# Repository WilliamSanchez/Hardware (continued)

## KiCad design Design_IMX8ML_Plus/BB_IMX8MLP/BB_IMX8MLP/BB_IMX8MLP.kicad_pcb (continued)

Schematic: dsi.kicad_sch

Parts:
C198, C199: 100nF; C_0402_1005Metric
J15: DSI; Hirose_FH12-24S-0.5SH_1x24-1MP_P0.50mm_Horizontal
R96, R97, R98, R99: 10K; R_0402_1005Metric
U21, U28, U29: D3V3F4U10LP-7; DFN10_U-DFN2510-10_DIO
U52: FXMA2102L8X; MICROPAK8_1P6X1P6_ONS

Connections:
/CSI_DSI/DSI/1v8: C198.1, R98.1, R99.1, U52.1 (VCCA)
/CSI_DSI/DSI/3v3: C199.1, R96.1, R97.1, U52.8 (VCCB)
/CSI_DSI/DSI/I2C2_DTA_LVDS0: R97.2, U52.6 (B1)
/CSI_DSI/DSI/I2C2_SCL: R98.2, U52.2 (A0)
/CSI_DSI/DSI/I2C2_SCL_LVDS0: R96.2, U52.7 (B0)
/CSI_DSI/DSI/I2C2_SDA: R99.2, U52.3 (A1)
DSI1_CLK_N: J15.3, U28.1 (I/O), U28.10 (I/O); also elsewhere on the board
DSI1_CLK_P: J15.2, U28.2 (I/O), U28.9 (I/O); also elsewhere on the board
DSI1_D0_N: J15.15, U29.5 (I/O), U29.6 (I/O); also elsewhere on the board
DSI1_D0_P: J15.14, U29.4 (I/O), U29.7 (I/O); also elsewhere on the board
DSI1_D1_N: J15.12, U29.2 (I/O), U29.9 (I/O); also elsewhere on the board
DSI1_D1_P: J15.11, U29.1 (I/O), U29.10 (I/O); also elsewhere on the board
DSI1_D2_N: J15.9, U21.5 (I/O), U21.6 (I/O); also elsewhere on the board
DSI1_D2_P: J15.8, U21.4 (I/O), U21.7 (I/O); also elsewhere on the board
DSI1_D3_N: J15.6, U21.2 (I/O), U21.9 (I/O); also elsewhere on the board
DSI1_D3_P: J15.5, U21.1 (I/O), U21.10 (I/O); also elsewhere on the board
GND: C198.2, C199.2, J15.1, J15.4, J15.7, J15.10, J15.13, J15.16, U52.4 (GND); also elsewhere on the board

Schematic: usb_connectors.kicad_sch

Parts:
C47, C51, C54, C55, C60, C61, C150, C151, C152, C153, C209: 100nF; C_0402_1005Metric
C48, C49, C56, C57, C194, C195, C208: 100uF; C_1210_3225Metric
C50, C58, C64: 1nF; C_0402_1005Metric
C52, C53, C59: 10uF; C_0603_1608Metric
FB1, FB2, FB3: 220R@100MHz; L_0603_1608Metric
J9: GSB311231HR; AMPHENOL_GSB311231HR; PARTREV D1
J14: USB_C_Receptacle; USB_C_Receptacle_Molex_105450-0101
R16: 887K; R_0402_1005Metric
R39, R40, R41, R61, R85: 100K; R_0402_1005Metric
R59, R60, R86: 0; R_0402_1005Metric
R84: 15K; R_0402_1005Metric
U9, U10, U40: PCMF3USB3S; Nexperia_WLCSP-15_6-3-6_2.37x1.17mm_Layout6x3_P0.4mm
U11, U12, U13: AOZ1353DI-01; DFN-12-1EP_3x3mm_P0.5mm_EP1.6x2.5mm
U56: TUSB321; Texas_X2QFN-12_1.6x1.6mm_P0.4mm

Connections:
5V_BB: C52.1, C53.1, C59.1, C208.1, C209.1, U11.10 (Vin), U11.11 (Vin), U11.12 (Vin), U12.10 (Vin), U12.11 (Vin), U12.12 (Vin), U13.10 (Vin), U13.11 (Vin), U13.12 (Vin), U56.12 (VDD); also elsewhere on the board
/USB/usb_connectors/1v8: R39.1, R40.1, R61.1
/USB/usb_connectors/USBH1D+: J14.A6 (D+), J14.B6 (D+), U40.C5 (CH3_OUT+)
/USB/usb_connectors/USBH1D-: J14.A7 (D-), J14.B7 (D-), U40.C6 (CH3_OUT-)
/USB/usb_connectors/USBH1SSRX+: J14.B11 (RX1+), U40.C3 (CH2_OUT+)
/USB/usb_connectors/USBH1SSRX-: J14.B10 (RX1-), U40.C4 (CH2_OUT-)
/USB/usb_connectors/USBH1SSTX+: J14.A2 (TX1+), U40.C1 (CH1_OUT+)
/USB/usb_connectors/USBH1SSTX-: J14.A3 (TX1-), U40.C2 (CH1_OUT-)
/USB/usb_connectors/USBH2D+: J9.12 (D+_2), U10.C1 (CH1_OUT+)
/USB/usb_connectors/USBH2D-: J9.11 (D-_2), U10.C2 (CH1_OUT-)
/USB/usb_connectors/USBH2SSRX+: J9.15 (SSRX+_2), U10.C5 (CH3_OUT+)
/USB/usb_connectors/USBH2SSRX-: J9.14 (SSRX-_2), U10.C6 (CH3_OUT-)
/USB/usb_connectors/USBH2SSTX+: J9.18 (SSTX+_2), U10.C3 (CH2_OUT+)
/USB/usb_connectors/USBH2SSTX-: J9.17 (SSTX-_2), U10.C4 (CH2_OUT-)
/USB/usb_connectors/USBH3D+: J9.3 (D+_1), U9.C1 (CH1_OUT+)
/USB/usb_connectors/USBH3D-: J9.2 (D-_1), U9.C2 (CH1_OUT-)
/USB/usb_connectors/USBH3SSRX+: J9.6 (SSRX+_1), U9.C5 (CH3_OUT+)
/USB/usb_connectors/USBH3SSRX-: J9.5 (SSRX-_1), U9.C6 (CH3_OUT-)
/USB/usb_connectors/USBH3SSTX+: J9.9 (SSTX+_1), U9.C3 (CH2_OUT+)
/USB/usb_connectors/USBH3SSTX-: J9.8 (SSTX-_1), U9.C4 (CH2_OUT-)
/USB/usb_connectors/USB_1_EN: R41.1, U13.9 (ENB)
/USB/usb_connectors/USB_1_ID: R40.2, U56.9 (ID)
/USB/usb_connectors/USB_1_OC#: R61.2, U13.4 (FLTB)
/USB/usb_connectors/USB_1_VBUS: R85.1, R86.1
/USB/usb_connectors/VBUS: C48.1, C49.1, C64.1, FB1.2, J14.A4 (VBUS), J14.A9 (VBUS), J14.B4 (VBUS), J14.B9 (VBUS), R16.1, R86.2
/USB/usb_connectors/VBUSH_1: C50.1, C194.1, C195.1, FB2.2, J9.1 (VBUS_1)
/USB/usb_connectors/VBUSH_2: C56.1, C57.1, C58.1, FB3.2, J9.10 (VBUS_2)
GND: C47.2, C48.2, C49.2, C50.2, C51.2, C52.2, C53.2, C54.2, C55.2, C56.2, C57.2, C58.2, C59.2, C60.2, C61.2, C64.2, C194.2, C195.2, C208.2, C209.2, J9.4 (GND_1), J9.7 (GND_DRAIN_1), J9.13 (GND_2), J9.16 (GND_DRAIN_2), R41.2, R84.2, R85.2, U9.B1 (GND_CH1), U9.B2 (GND_CH2), U9.B3 (GND_CH3), U10.B1 (GND_CH1), U10.B2 (GND_CH2), U10.B3 (GND_CH3), U11.7 (GND), U11.13 (EXP), U12.7 (GND), U12.13 (EXP), U13.7 (GND), U13.13 (EXP), U40.B1 (GND_CH1), U40.B2 (GND_CH2), U40.B3 (GND_CH3), U56.10 (GND); also elsewhere on the board
unnamed: C47.1, FB2.1, U11.1 (Vout), U11.2 (Vout), U11.3 (Vout)
unnamed: C55.1, FB3.1, U12.1 (Vout), U12.2 (Vout), U12.3 (Vout)
unnamed: C61.1, FB1.1, U13.1 (Vout), U13.2 (Vout), U13.3 (Vout)
unnamed: J9.SH1 (SHIELD), J9.SH2 (SHIELD), J9.SH3 (SHIELD), J9.SH4 (SHIELD)
unnamed: J14.A5 (CC1), U56.1 (CC1)
unnamed: J14.B5 (CC2), U56.2 (CC2)
unnamed: J14.A1 (GND), J14.A12 (GND), J14.B1 (GND), J14.B12 (GND)
unnamed: C151.1, U9.A3 (CH2_IN+)
unnamed: C150.1, U9.A4 (CH2_IN-)
unnamed: C153.1, U10.A3 (CH2_IN+)
unnamed: C152.1, U10.A4 (CH2_IN-)
unnamed: R60.1, U11.4 (FLTB)
unnamed: C51.1, U11.5 (SS)
unnamed: R59.1, U12.4 (FLTB)
unnamed: C54.1, U12.5 (SS)
unnamed: R84.1, U13.8 (ILIM)
unnamed: C60.1, U13.5 (SS)
unnamed: R16.2, U56.5 (VBUS_DET)
unnamed: R39.2, U56.6 (~VCONN_FAULT)
USB1_D_N: U40.A6 (CH3_IN-); also elsewhere on the board
USB1_D_P: U40.A5 (CH3_IN+); also elsewhere on the board
USB1_RX_N: U40.A4 (CH2_IN-); also elsewhere on the board
USB1_RX_P: U40.A3 (CH2_IN+); also elsewhere on the board
USB1_TX_N: U40.A2 (CH1_IN-); also elsewhere on the board
USB1_TX_P: U40.A1 (CH1_IN+); also elsewhere on the board
USBH2_D+: U10.A1 (CH1_IN+); also elsewhere on the board
USBH2_D-: U10.A2 (CH1_IN-); also elsewhere on the board
USBH2_PRT_CTL: R59.2, U12.8 (ILIM); also elsewhere on the board
USBH2_SSRX+: U10.A5 (CH3_IN+); also elsewhere on the board
USBH2_SSRX-: U10.A6 (CH3_IN-); also elsewhere on the board
USBH2_SSTX+: C153.2; also elsewhere on the board
USBH2_SSTX-: C152.2; also elsewhere on the board
USBH3_D+: U9.A1 (CH1_IN+); also elsewhere on the board
USBH3_D-: U9.A2 (CH1_IN-); also elsewhere on the board
USBH3_PRT_CTL: R60.2, U11.8 (ILIM); also elsewhere on the board
USBH3_SSRX+: U9.A5 (CH3_IN+); also elsewhere on the board
USBH3_SSRX-: U9.A6 (CH3_IN-); also elsewhere on the board
USBH3_SSTX+: C151.2; also elsewhere on the board
USBH3_SSTX-: C150.2; also elsewhere on the board

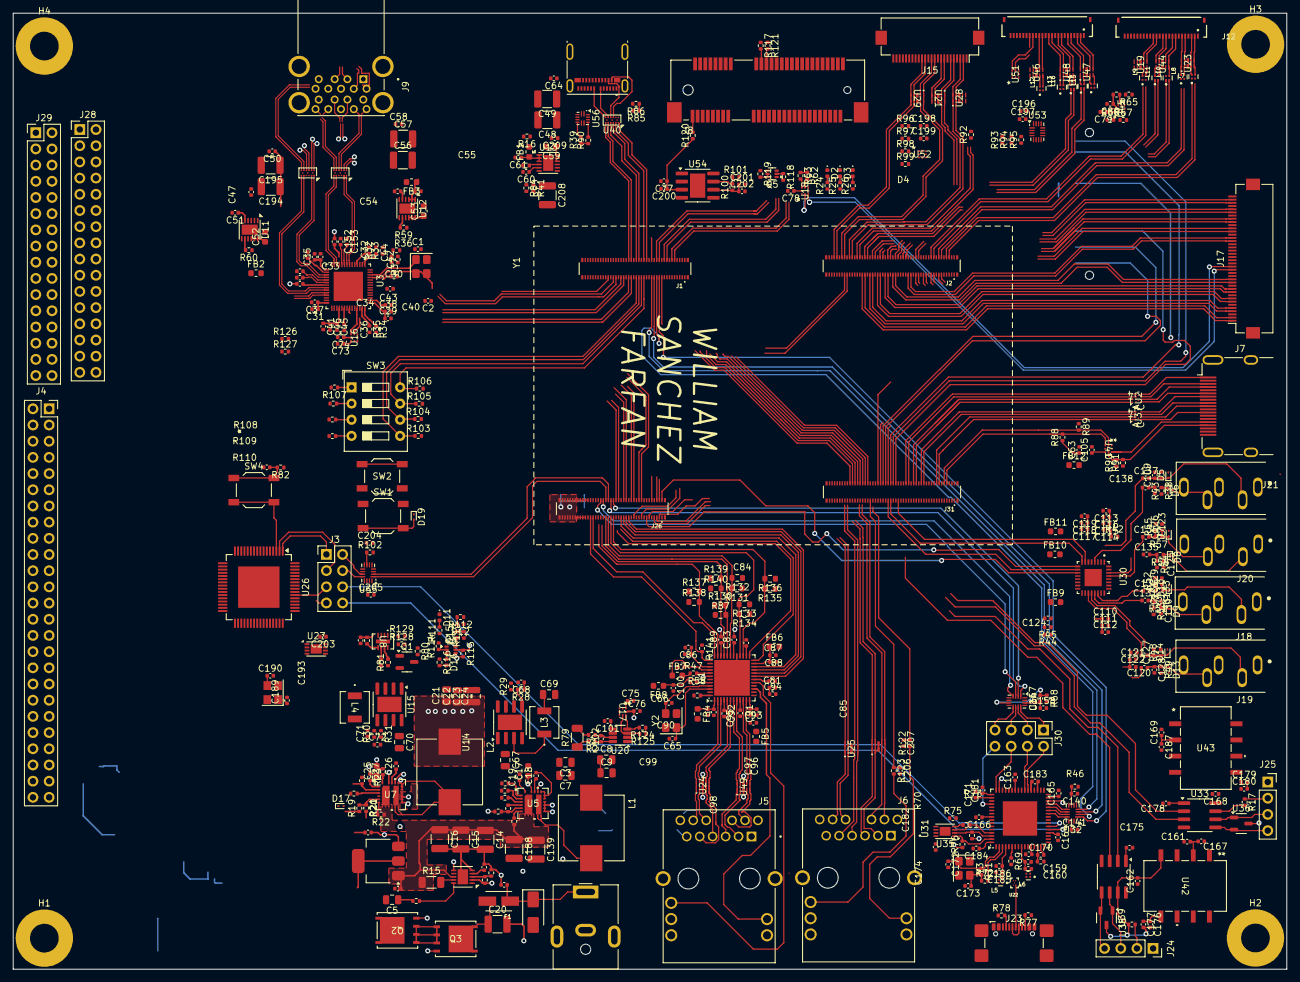
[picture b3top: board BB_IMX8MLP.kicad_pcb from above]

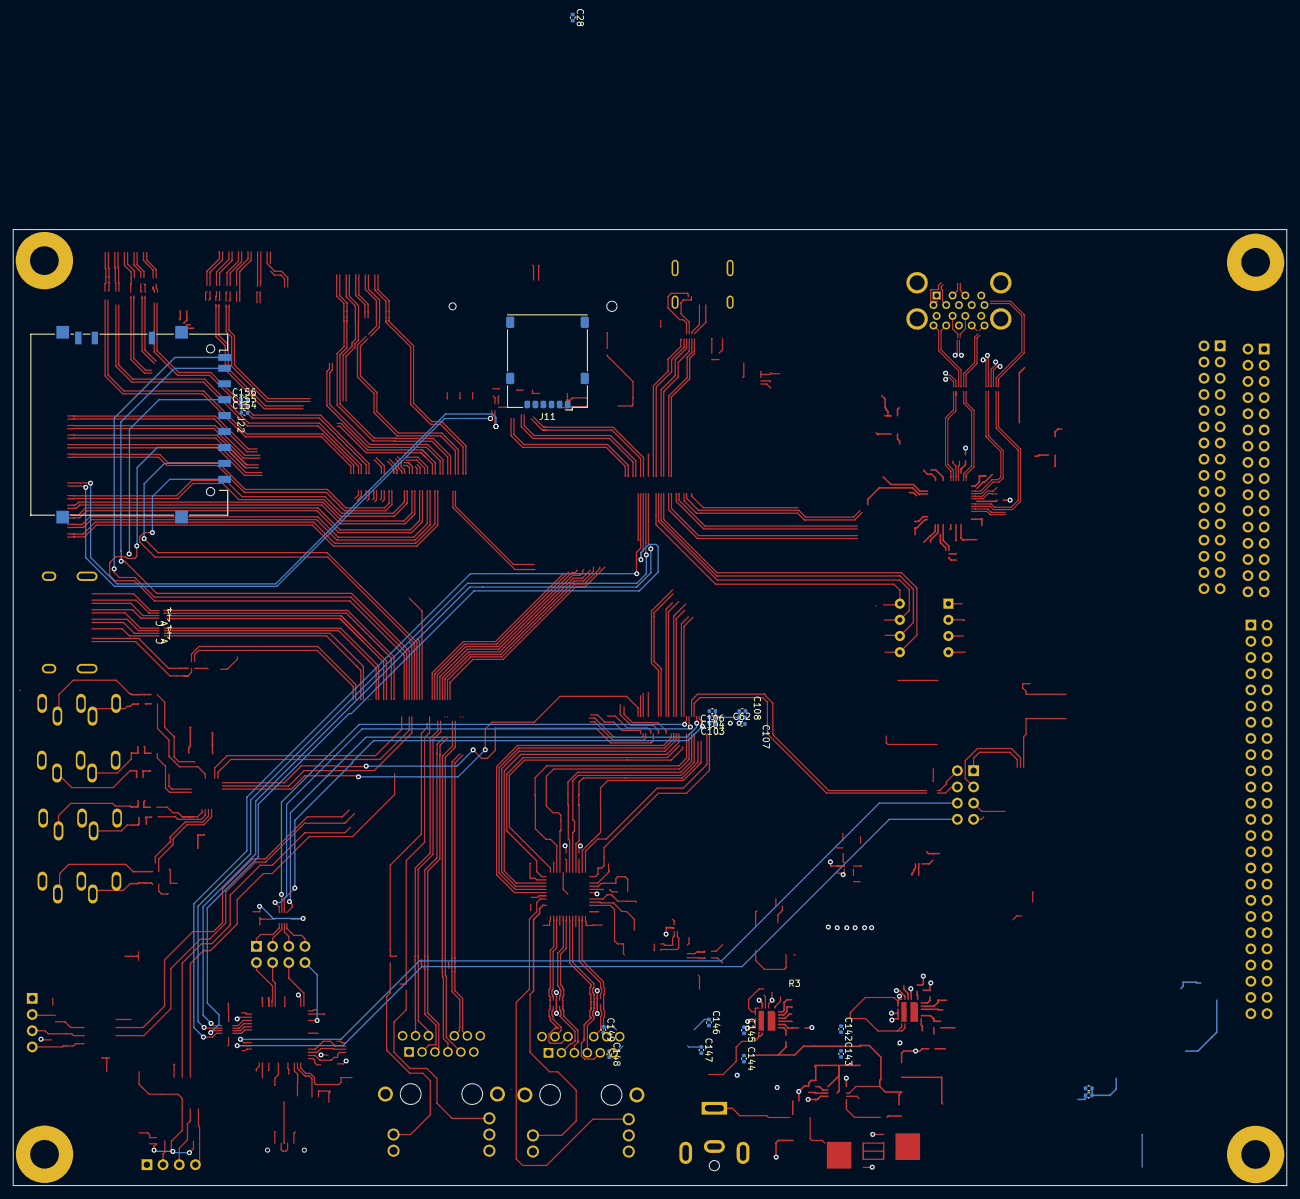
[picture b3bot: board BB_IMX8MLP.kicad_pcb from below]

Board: 4 copper layers, 199.8 x 150.0 mm, 496 parts (22 on the bottom side), 499 nets.

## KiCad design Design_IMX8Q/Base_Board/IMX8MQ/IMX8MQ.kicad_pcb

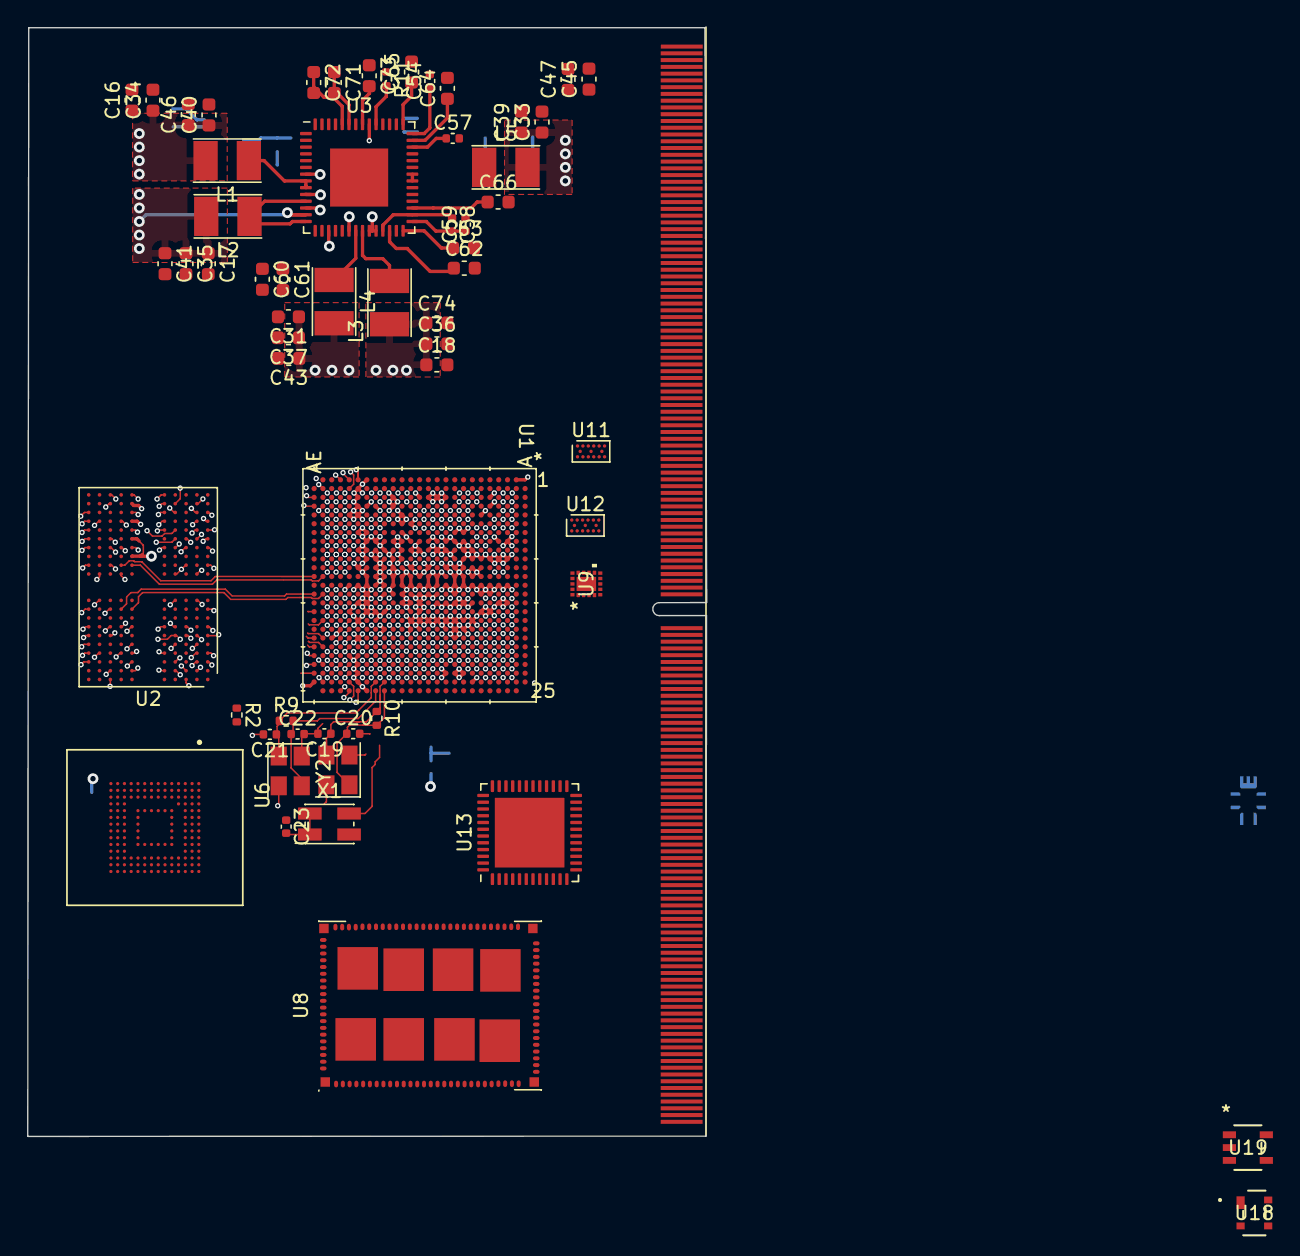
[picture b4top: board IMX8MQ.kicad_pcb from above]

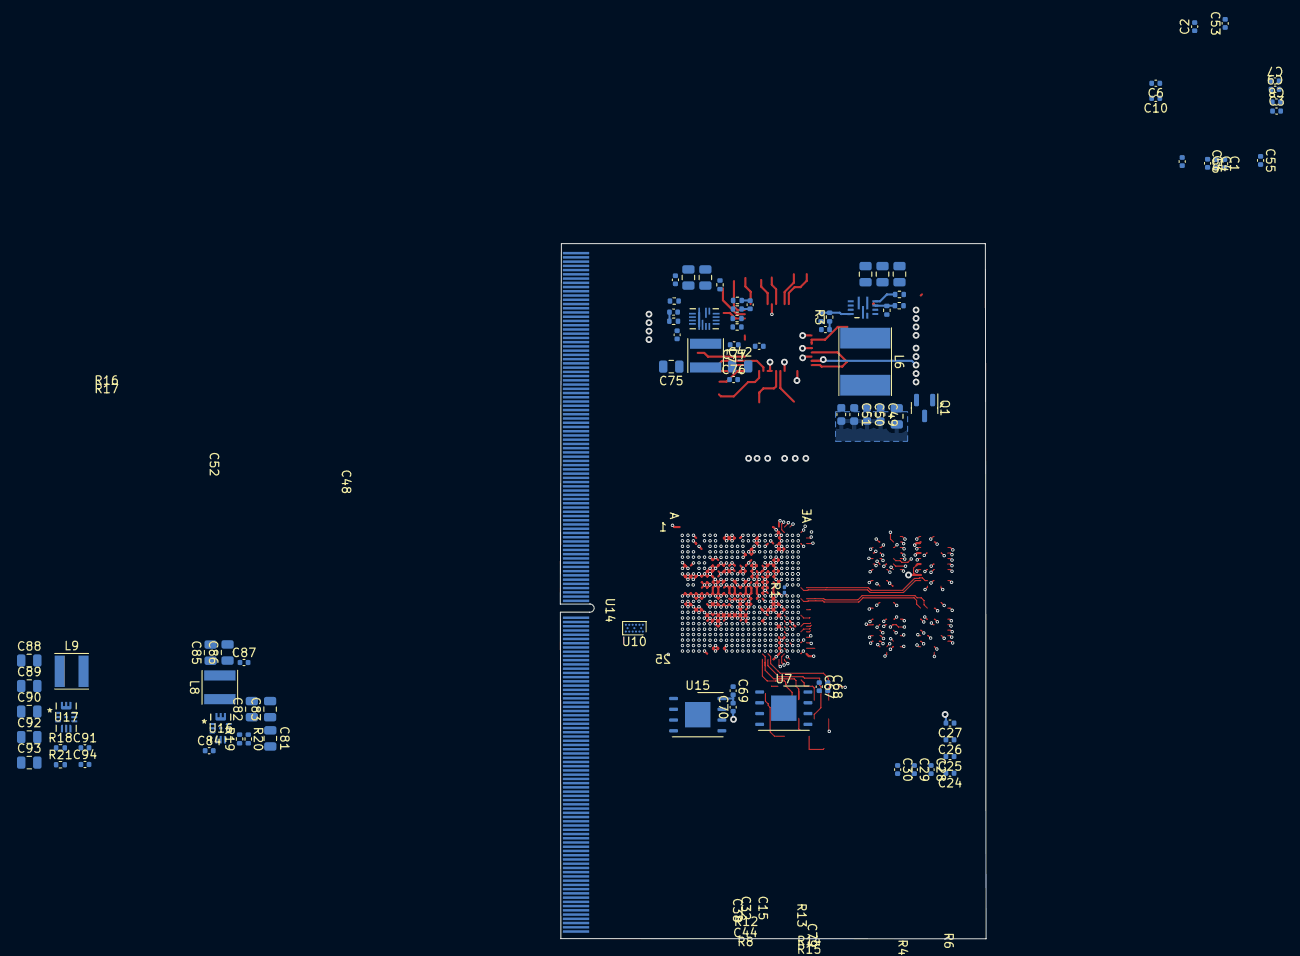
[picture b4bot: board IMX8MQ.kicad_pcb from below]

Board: 8 copper layers, 50.2 x 82.0 mm, 147 parts (87 on the bottom side), 295 nets.

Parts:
C1, C2, C3, C4, C5, C6, C7, C8, C9, C10: 4.7uF; C_0402_1005Metric
C11: 22uF; C_0402_1005Metric
C12, C13, C14, C81, C82, C83, C88, C89, C90: 22uF; C_0805_2012Metric
C15, C32, C42, C75, C85, C86, C92, C93: 10uF; C_0805_2012Metric
C16, C17, C18, C31, C33, C34, C35, C36, C37, C39, C40, C41, C43, C45, C46, C47, C49, C50, C51, C52, C74: 22uF; C_0603_1608Metric
C19, C20, C21, C22: 10pF; C_0402_1005Metric
C23, C25, C26, C27, C28, C29, C38, C54, C58, C59, C67, C68, C69, C70, C76, C87, C94: 0.1uF; C_0402_1005Metric
C24, C30: 4.7F; C_0402_1005Metric
C44, C53, C77, C78, C80: 1uF; C_0402_1005Metric
C48: 220uF; C_0805_2012Metric
C55, C56, C57: 0.47uF; C_0402_1005Metric
C60, C61, C62, C63, C64, C65: 4.7uF; C_0603_1608Metric
C66, C71, C73: 1uF; C_0603_1608Metric
C72: 0.22uF; C_0603_1608Metric
C79, C84, C91: 5.6uF; C_0402_1005Metric
L1, L2, L3, L4, L5: 1uH; L_Taiyo-Yuden_NR-30xx_HandSoldering
L6: 1.5uH; L_Taiyo-Yuden_NR-60xx_HandSoldering
L7, L8, L9: 4.7uH; L_Taiyo-Yuden_NR-40xx
Q1: AO3401A; SOT-23
R1: 240 1%; R_0201_0603Metric
R2: 240; R_0402_1005Metric
R3, R4: 100k; R_0402_1005Metric
R5: 1.5M; R_0402_1005Metric
R6: 44.2K; R_0402_1005Metric
R7: 9.53k; R_0402_1005Metric
R8, R14, R15, R18, R19, R20, R21: 10K; R_0402_1005Metric
R9, R10: 1M; R_0402_1005Metric
R11: 10.0k; R_0402_1005Metric
R12, R16, R17: 0K; R_0402_1005Metric
R13: 27K; R_0402_1005Metric
U1: MIMX8MQ6CVAHZAB
U2: IS43LQ32256A-062BLI; BGA-200_10.0x14.5mm_Layout12x22_P0.80x0.65mm
U3: QFN-56-1EP_8x8mm_P0.5mm_EP4.3x4.3mm
U4: MP8759GD-Z
U5: MP2263GD-Z; MP2263
U6: SDINBDG4-8G; BGA153C50P14X14_1300X1150X80N
U7, U15: MT25QUxxxxxx1xW7; W-PDFN-8-1EP_6x5mm_P1.27mm_EP3x3mm
U8: WG3221-00_DTS_R01
U9: PTN36043ABXY; DHX2QFN18_SOT1442-1_NXP
U10, U11, U12: PCMF3USB3S; Nexperia_WLCSP-15_6-3-6_2.37x1.17mm_Layout6x3_P0.4mm
U13: KSZ9131RNXI; VQFN-48-1EP_7x7mm_P0.5mm_EP5.15x5.15mm
U14: IMX6ModuleConector_300; IMX6QPModule_R300
U16, U17: MP2147GD-P
U18: UM805RE
U19: LDCL015MR
X1: ABLNO; Oscillator_SMD_EuroQuartz_XO32-4Pin_3.2x2.5mm_HandSoldering
Y1: 27MHz; Crystal_SMD_3225-4Pin_3.2x2.5mm
Y2: 25MHz; Crystal_SMD_3225-4Pin_3.2x2.5mm

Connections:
CA0_A: U1.AD17 (DRAM_AC08), U2.H2 (CA0_A)
CA0_B: U1.AE8 (DRAM_AC32), U2.R2 (CA0_B)
CA1_A: U1.AE16 (DRAM_AC09), U2.J2 (CA1_A)
CA1_B: U1.AE9 (DRAM_AC33), U2.P2 (CA1_B)
CA2_A: U1.AD20 (DRAM_AC10), U2.H9 (CA2_A)
CA2_B: U1.AC7 (DRAM_AC28), U2.R9 (CA2_B)
CA3_A: U1.AE20 (DRAM_AC11), U2.H10 (CA3_A)
CA3_B: U1.AE7 (DRAM_AC29), U2.R10 (CA3_B)
CA4_A: U1.AD19 (DRAM_AC12), U2.H11 (CA4_A)
CA4_B: U1.AE6 (DRAM_AC30), U2.R11 (CA4_B)
CA5_A: U1.AE19 (DRAM_AC13), U2.J11 (CA5_A)
CA5_B: U1.AD6 (DRAM_AC31), U2.P11 (CA5_B)
CK_A+: U1.AD14 (DRAM_AC04), U2.J8 (CK_T_A)
CK_A-: U1.AE14 (DRAM_AC05), U2.J9 (CK_C_A)
CK_B+: U1.AD12 (DRAM_AC24), U2.P8 (CK_T_B)
CK_B-: U1.AE12 (DRAM_AC25), U2.P9 (CK_C_B)
DCDC_3V3: C1.1, C2.1, C3.1, C4.1, C5.1, C6.1, C7.1, C8.1, C9.1, C10.1, C48.1, C49.1, C50.1, C51.1, C52.1, C53.1, C55.1, C56.1, C81.1, C82.1, C83.1, C88.1, C89.1, C90.1, L6.2, Q1.3 (D), R6.1, U3.7 (SW1AIN), U3.10 (SW1BIN), U3.12 (SW1CIN), U3.17 (VIN1), U3.20 (SW4IN), U3.23 (SW2IN), U3.24 (SW2IN), U3.27 (VIN2), U3.34 (SW3BIN), U3.37 (SW3AIN), U3.45 (SWBSTIN), U3.50 (VIN), U4.5 (VOUT), U16.8 (VIN), U16.13 (VIN), U17.8 (VIN), U17.13 (VIN)
DCDC_5V: C42.1, C75.1, C76.1, L7.2, R14.2
DMI0_A: U1.AD23 (DRAM_DM0), U2.C3 (DMI0_A)
DMI0_B: U1.AD3 (DRAM_DM2), U2.Y3 (DMI0_B)
DMI1_A: U1.AB20 (DRAM_DM1), U2.C10 (DMI1_A)
DMI1_B: U1.AB6 (DRAM_DM3), U2.Y10 (DMI1_B)
DQS0_A+: U1.AC24 (DRAM_DQS0_P), U2.D3 (DQS0_T_A)
DQS0_A-: U1.AC25 (DRAM_DQS0_N), U2.E3 (DQS0_C_A)
DQS0_B+: U1.AC2 (DRAM_DQS2_P), U2.W3 (DQS0_T_B)
DQS0_B-: U1.AC1 (DRAM_DQS2_N), U2.V3 (DQS0_C_B)
DQS1_A+: U1.AB21 (DRAM_DQS1_P), U2.D10 (DQS1_T_A)
DQS1_A-: U1.AC21 (DRAM_DQS1_N), U2.E10 (DQS1_C_A)
DQS1_B+: U1.AB5 (DRAM_DQS3_P), U2.W10 (DQS1_T_B)
DQS1_B-: U1.AC5 (DRAM_DQS3_N), U2.V10 (DQS1_C_B)
DRAM_DATA0_A: U1.AE23 (DRAM_DQ00), U2.B2 (DQ0_A)
DRAM_DATA0_B: U1.AE3 (DRAM_DQ16), U2.AA2 (DQ0_B)
DRAM_DATA1_A: U1.AD24 (DRAM_DQ01), U2.C2 (DQ1_A)
DRAM_DATA1_B: U1.AD2 (DRAM_DQ17), U2.Y2 (DQ1_B)
DRAM_DATA2_A: U1.AE22 (DRAM_DQ02), U2.E2 (DQ2_A)
DRAM_DATA2_B: U1.AE4 (DRAM_DQ18), U2.V2 (DQ2_B)
DRAM_DATA3_A: U1.AD22 (DRAM_DQ03), U2.F2 (DQ3_A)
DRAM_DATA3_B: U1.AD4 (DRAM_DQ19), U2.U2 (DQ3_B)
DRAM_DATA4_A: U1.AA24 (DRAM_DQ04), U2.F4 (DQ4_A)
DRAM_DATA4_B: U1.AA2 (DRAM_DQ20), U2.U4 (DQ4_B)
DRAM_DATA5_A: U1.Y25 (DRAM_DQ05), U2.E4 (DQ5_A)
DRAM_DATA5_B: U1.Y1 (DRAM_DQ21), U2.V4 (DQ5_B)
DRAM_DATA6_A: U1.AA25 (DRAM_DQ06), U2.C4 (DQ6_A)
DRAM_DATA6_B: U1.AA1 (DRAM_DQ22), U2.Y4 (DQ6_B)
DRAM_DATA7_A: U1.AB25 (DRAM_DQ07), U2.B4 (DQ7_A)
DRAM_DATA7_B: U1.AB1 (DRAM_DQ23), U2.AA4 (DQ7_B)
DRAM_DATA8_A: U1.AB22 (DRAM_DQ08), U2.B11 (DQ8_A)
DRAM_DATA8_B: U1.AB4 (DRAM_DQ24), U2.AA11 (DQ8_B)
DRAM_DATA9_A: U1.AA22 (DRAM_DQ09), U2.C11 (DQ9_A)
DRAM_DATA9_B: U1.AA4 (DRAM_DQ25), U2.Y11 (DQ9_B)
DRAM_DATA10_A: U1.AA23 (DRAM_DQ10), U2.E11 (DQ10_A)
DRAM_DATA10_B: U1.AA3 (DRAM_DQ26), U2.V11 (DQ10_B)
DRAM_DATA11_A: U1.AA20 (DRAM_DQ11), U2.F11 (DQ11_A)
DRAM_DATA11_B: U1.AA6 (DRAM_DQ27), U2.U11 (DQ11_B)
DRAM_DATA12_A: U1.AA18 (DRAM_DQ12), U2.F9 (DQ12_A)
DRAM_DATA12_B: U1.AA8 (DRAM_DQ28), U2.U9 (DQ12_B)
DRAM_DATA13_A: U1.AB19 (DRAM_DQ13), U2.E9 (DQ13_A)
DRAM_DATA13_B: U1.AB7 (DRAM_DQ29), U2.V9 (DQ13_B)
DRAM_DATA14_A: U1.AA19 (DRAM_DQ14), U2.C9 (DQ14_A)
DRAM_DATA14_B: U1.AA7 (DRAM_DQ30), U2.Y9 (DQ14_B)
DRAM_DATA15_A: U1.AA17 (DRAM_DQ15), U2.B9 (DQ15_A)
DRAM_DATA15_B: U1.AA9 (DRAM_DQ31), U2.AA9 (DQ15_B)
ECSPI2_MISO: U1.B5 (ECSPI2_MISO), U14.57
ECSPI2_MOSI: U1.E5 (ECSPI2_MOSI), U14.53
ECSPI2_SCLK: U1.C5 (ECSPI2_SCLK), U14.55
ECSPI2_SS0: U1.A5 (ECSPI2_SS0), U14.59
ENET_MDC: U1.N20 (ENET_MDC), U13.36 (MDC)
ENET_MDIO: U1.N19 (ENET_MDIO), U13.37 (MDIO)
ENET_RD0: U1.U19 (ENET_RD0), U13.32 (RXD0/MODE0)
ENET_RD1: U1.U21 (ENET_RD1), U13.31 (RXD1/MODE1)
ENET_RD2: U1.U20 (ENET_RD2), U13.28 (RXD2/MODE2)
ENET_RD3: U1.V19 (ENET_RD3), U13.27 (RXD3/MODE3)
ENET_RXC: U1.T20 (ENET_RXC), U13.35 (RXC/PHYAD2)
ENET_RX_CTL: U1.T21 (ENET_RX_CTL), U13.33 (RX_CTL/CLK125_EN)
ENET_TD0: U1.R20 (ENET_TD0), U13.19 (TXD0)
ENET_TD1: U1.R21 (ENET_TD1), U13.20 (TXD1)
ENET_TD2: U1.R19 (ENET_TD2), U13.21 (TXD2)
ENET_TD3: U1.P20 (ENET_TD3), U13.22 (TXD3)
ENET_TXC: U1.T19 (ENET_TXC), U13.24 (TXC)
ENET_TX_CL: U1.P19 (ENET_TX_CTL), U13.25 (TX_CTL)
GND: C1.2, C2.2, C3.2, C4.2, C5.2, C6.2, C7.2, C8.2, C9.2, C10.2, C11.2, C12.2, C13.2, C14.2, C15.2, C16.2, C17.2, C18.2, C19.2, C20.2, C21.2, C22.2, C23.1, C24.1, C25.1, C26.1, C27.1, C28.1, C29.1, C30.1, C31.2, C32.2, C33.2, C34.2, C35.2, C36.2, C37.2, C38.2, C39.2, C40.2, C41.2, C42.2, C43.2, C44.2, C45.2, C46.2, C47.2, C48.2, C49.2, C50.2, C51.2, C52.2, C53.2, C54.2, C55.2, C56.2, C57.2, C59.2, C60.2, C61.2, C62.2, C63.2, C64.2, C65.2, C66.2, C67.1, C68.1, C69.1, C70.1, C71.1, C72.1, C73.1, C74.2, C75.2, C76.2, C78.2, C80.2, C81.2, C82.2, C83.2, C85.2, C86.2, C87.2, C88.2, C89.2, C90.2, C92.2, C93.2, C94.2, R1.2, R4.2, R7.2, R11.1, R13.1, R17.1, R18.1, R19.1, U1.A2 (VSS), U1.A24 (VSS), U1.AA5 (VSS), U1.AA16 (VSS), U1.AA21 (VSS), U1.AB2 (VSS), U1.AB9 (VSS), U1.AB11 (VSS), U1.AB18 (VSS), U1.AB24 (VSS), U1.AC4 (VSS), U1.AC19 (VSS), U1.AC22 (VSS), U1.AD1 (VSS), U1.AD7 (VSS), U1.AD9 (VSS), U1.AD11 (VSS), U1.AD13 (VSS), U1.AD16 (VSS), U1.AD25 (VSS), U1.AE2 (VSS), U1.AE5 (VSS), U1.AE21 (VSS), U1.AE24 (VSS), U1.B1 (VSS), U1.B25 (VSS), U1.C8 (VSS), U1.C10 (VSS), U1.C13 (VSS), U1.C15 (VSS), U1.C24 (VSS), U1.D10 (VSS), U1.D13 (VSS), U1.D15 (VSS), U1.D23 (VSS), U1.E4 (VSS), U1.E10 (VSS), U1.E13 (VSS), U1.E14 (VSS), U1.E16 (VSS), U1.E19 (VSS), U1.E20 (VSS), U1.E21 (VSS), U1.E22 (VSS), U1.E23 (VSS), U1.F10 (VSS), U1.F13 (VSS), U1.F14 (VSS), U1.F16 (VSS), U1.F20 (VSS), U1.G9 (VSS), U1.G10 (VSS), U1.G13 (VSS), U1.G17 (VSS), U1.G18 (VSS), U1.G24 (VSS), U1.H8 (VSS), U1.H9 (VSS), U1.H10 (VSS), U1.H11 (VSS), U1.H12 (VSS), U1.H13 (VSS), U1.H17 (VSS), U1.H18 (VSS), U1.J3 (VSS), U1.J8 (VSS), U1.J11 (VSS), U1.J12 (VSS), U1.J13 (VSS), U1.J14 (VSS), U1.J17 (VSS), U1.J18 (VSS), U1.J19 (VSS), U1.K8 (VSS), U1.K11 (VSS), U1.K13 (VSSA_FPLL_ARM), U1.K17 (VSS), U1.K18 (VSS), U1.K23 (VSS), U1.L8 (VSS), U1.L11 (VSS), U1.L14 (VSS), U1.L17 (VSS), U1.M8 (VSS), U1.M11 (VSS), U1.M14 (VSS), U1.M17 (VSS), U1.N3 (VSS), U1.N12 (VSSA_SPLL_VIDEO2), U1.N14 (VSS), U1.N15 (VSS), U1.N16 (VSS), U1.N17 (VSS), U1.N18 (VSS), U1.P6 (VSS), U1.P8 (VSS), U1.P11 (VSS), U1.P14 (VSS), U1.P17 (VSS), U1.P18 (VSS), U1.P23 (VSS), U1.R7 (VSS), U1.T3 (VSS), U1.T4 (VSS), U1.T9 (VSS), U1.T10 (VSS), U1.T11 (VSS), U1.T12 (VSS), U1.T13 (VSS), U1.T14 (VSSA_SPLL_DRAM), U1.U8 (VSS), U1.U9 (VSS), U1.U15 (VSS), U1.U16 (VSSA_FPLL), U1.U18 (VSS), U1.V4 (VSS), U1.V8 (VSS), U1.V16 (VSS), U1.V17 (VSSA_SPLL), U1.V23 (VSSA_XTAL_25M), U1.W1 (VSS), U1.W7 (VSS), U1.W8 (VSS), U1.W9 (VSS), U1.W10 (VSS), U1.W11 (VSS), U1.W12 (VSS), U1.W13 (VSS), U1.W14 (VSS), U1.W15 (VSS), U1.W16 (VSS), U1.W22 (VSSA_XTAL_27M), U1.W25 (VSS), U1.Y2 (VSS), U1.Y3 (VSS), U1.Y4 (VSS), U1.Y5 (VSS), U1.Y7 (VSS), U1.Y9 (VSS), U1.Y11 (VSS), U1.Y13 (VSS), U1.Y15 (VSS), U1.Y17 (VSS), U1.Y19 (VSS), U1.Y21 (VSS), U1.Y22 (VSS), U1.Y23 (VSS), U1.Y24 (VSS), U2.A3 (VSS), U2.A10 (VSS), U2.AB3 (VSS), U2.AB5 (VSS), U2.AB8 (VSS), U2.AB10 (VSS), U2.C1 (VSS), U2.C5 (VSS), U2.C8 (VSS), U2.C12 (VSS), U2.D2 (VSS), U2.D4 (VSS), U2.D9 (VSS), U2.D11 (VSS), U2.E1 (VSS), U2.E5 (VSS), U2.E8 (VSS), U2.E12 (VSS), U2.G1 (VSS), U2.G3 (VSS), U2.G5 (VSS), U2.G8 (VSS), U2.G10 (VSS), U2.G12 (VSS), U2.J1 (VSS), U2.J3 (VSS), U2.J10 (VSS), U2.J12 (VSS), U2.K2 (VSS), U2.K4 (VSS), U2.K9 (VSS), U2.K11 (VSS), U2.N2 (VSS), U2.N4 (VSS), U2.N9 (VSS), U2.N11 (VSS), U2.P1 (VSS), U2.P3 (VSS), U2.P10 (VSS), U2.P12 (VSS), U2.T1 (VSS), U2.T3 (VSS), U2.T5 (VSS), U2.T8 (VSS), U2.T10 (VSS), U2.T12 (VSS), U2.V1 (VSS), U2.V5 (VSS), U2.V8 (VSS), U2.V12 (VSS), U2.W2 (VSS), U2.W4 (VSS), U2.W9 (VSS), U2.W11 (VSS), U2.Y1 (VSS), U2.Y5 (VSS), U2.Y8 (VSS), U2.Y12 (VSS), U3.15 (GNDREF1), U3.32 (SW3VSSSNS), U3.48 (GNDREF), U3.57 (EPGND), U4.2 (PGND), U4.10 (AGND), U5.3 (PGND), U5.8 (PGND), U5.12 (AGND), U6.A6 (VSS_A6), U6.C4 (VSSQ_C4), U6.E7 (VSS_E7), U6.G5 (VSS_G5), U6.H10 (VSS_H10), U6.J5 (VSS_J5), U6.K8 (VSS_K8), U6.N2 (VSSQ_N2), U6.N5 (VSSQ_N5), U6.P4 (VSSQ_P4), U6.P6 (VSSQ_P6), U7.4 (VSS), U7.9 (PAD), U8.6 (GND), U8.17 (GND), U8.20 (GND), U8.23 (GND), U8.26 (GND), U8.32 (GND), U8.35 (GND), U8.38 (GND), U8.41 (GND), U8.62 (GND), U8.68 (GND), U8.71 (GND), U8.75 (GND), U8.76 (GND), U8.77 (GND), U8.78 (GND), U8.79 (GND), U8.80 (GND), U8.81 (GND), U8.82 (GND), U8.83 (GND), U8.84 (GND), U8.85 (GND), U8.86 (GND), U8.87 (GND), U8.88 (GND), U8.89 (GND), U8.90 (GND), U8.91 (GND), U8.92 (GND), U8.93 (GND), U8.94 (GND), U8.95 (GND), U8.96 (GND), U8.97 (GND), U8.98 (GND), U8.99 (GND), U8.100 (GND), U8.101 (GND), U8.102 (GND), U8.103 (GND), U8.105 (GND), U8.106 (GND), U8.107 (GND), U8.108 (GND), U15.4 (VSS), U15.9 (PAD), U16.10 (GND), U16.11 (GND), U16.12 (GND), U17.10 (GND), U17.11 (GND), U17.12 (GND), X1.2 (GND), Y1.2, Y1.4, Y2.2, Y2.4
HDMI_AUX_+: U1.V1 (HDMI_AUX_P), U14.46
HDMI_AUX_-: U1.V2 (HDMI_AUX_N), U14.48
HDMI_CEC: U1.W3 (HDMI_CEC), U14.52
HDMI_DDC_SCL: U1.R3 (HDMI_DDC_SCL), U14.36
HDMI_DDC_SDA: U1.P3 (HDMI_DDC_SDA), U14.30
HDMI_HPD: U1.W2 (HDMI_HPD), U14.50
HDMI_REFCLK_+: U1.R2 (HDMI_REFCLK_P), U14.34
HDMI_REFCLK_-: U1.R1 (HDMI_REFCLK_N), U14.16 (32)
HDMI_REXT: U1.P1 (HDMI_REXT), U14.28
HDMI_TX_LN_0_+: U1.T1 (HDMI_TX_P_LN_0), U14.38
HDMI_TX_LN_0_-: U1.T2 (HDMI_TX_M_LN_0), U14.40
HDMI_TX_LN_1_+: U1.U2 (HDMI_TX_P_LN_1), U14.42
HDMI_TX_LN_1_-: U1.U1 (HDMI_TX_M_LN_1), U14.44
HDMI_TX_LN_2_+: U1.N2 (HDMI_TX_P_LN_2), U14.26
HDMI_TX_LN_2_-: U1.N1 (HDMI_TX_M_LN_2), U14.24
HDMI_TX_LN_3_+: U1.M1 (HDMI_TX_P_LN_3), U14.20
HDMI_TX_LN_3_-: U1.M2 (HDMI_TX_M_LN_3), U14.22
I2C1_SCL: U1.E7 (I2C1_SCL), U14.63
I2C1_SDA: U1.E8 (I2C1_SDA), U14.65
I2C2_SCL: U1.G7 (I2C2_SCL), U14.69
I2C2_SDA: U1.F7 (I2C2_SDA), U14.67
I2C3_SCL: U1.G8 (I2C3_SCL), U14.73
I2C3_SDA: U1.E9 (I2C3_SDA), U14.71
I2C4_SCL: U1.F8 (I2C4_SCL), U14.75
I2C4_SDA: U1.F9 (I2C4_SDA), U14.77
JTAG_MOD: U1.U7 (JTAG_MOD), U14.96
JTAG_TCK: U1.T5 (JTAG_TCK), U14.90
JTAG_TDI: U1.W5 (JTAG_TDI), U14.100
JTAG_TDO: U1.U5 (JTAG_TDO), U14.92
JTAG_TMS: U1.V5 (JTAG_TMS), U14.98
JTAG_TRST_B: U1.U6 (JTAG_TRST_B), U14.94
MIPI_CSI1_D0_+: U1.B23 (MIPI_CSI1_D0_P), U14.174
MIPI_CSI1_D1_+: U1.D22 (MIPI_CSI1_D1_P), U14.178
MIPI_CSI1_D1_-: U1.C22 (MIPI_CSI1_D1_N), U14.176
MIPI_CSI1_D2_+: U1.C23 (MIPI_CSI1_D2_P), U14.182
MIPI_CSI1_D2_-: U1.B24 (MIPI_CSI1_D2_N), U14.180
MIPI_CSI1_D3_+: U1.D21 (MIPI_CSI1_D3_P), U14.186
MIPI_CSI1_D3_-: U1.C21 (MIPI_CSI1_D3_N), U14.184
MIPI_CSI2_CLK+: U1.B19 (MIPI_CSI2_CLK_P), U14.204
MIPI_CSI2_CLK-: U1.A19 (MIPI_CSI2_CLK_N), U14.202
MIPI_CSI2_D0_+: U1.D20 (MIPI_CSI2_D0_P), U14.220
MIPI_CSI2_D0_-: U1.C20 (MIPI_CSI2_D0_N), U14.218
MIPI_CSI2_D1_+: U1.B20 (MIPI_CSI2_D1_P), U14.216
MIPI_CSI2_D1_-: U1.A20 (MIPI_CSI2_D1_N), U14.214
MIPI_CSI2_D2_+: U1.B21 (MIPI_CSI2_D2_P), U14.212
MIPI_CSI2_D2_-: U1.A21 (MIPI_CSI2_D2_N), U14.210
MIPI_CSI2_D3_+: U1.D19 (MIPI_CSI2_D3_P), U14.208
MIPI_CSI2_D3_-: U1.C19 (MIPI_CSI2_D3_N), U14.206
MIPI_DSI_CLK+: U1.D16 (MIPI_DSI_CLK_P), U14.126
MIPI_DSI_CLK-: U1.C16 (MIPI_DSI_CLK_N), U14.124
MIPI_DSI_D0_+: U1.B17 (MIPI_DSI_D0_P), U14.142
MIPI_DSI_D0_-: U1.A17 (MIPI_DSI_D0_N), U14.140
MIPI_DSI_D1_+: U1.B16 (MIPI_DSI_D1_P), U14.138
MIPI_DSI_D1_-: U1.A16 (MIPI_DSI_D1_N), U14.136
MIPI_DSI_D2_+: U1.B18 (MIPI_DSI_D2_P), U14.134
MIPI_DSI_D2_-: U1.A18 (MIPI_DSI_D2_N), U14.132
MIPI_DSI_D3_+: U1.B15 (MIPI_DSI_D3_P), U14.130
MIPI_DSI_D3_-: U1.A15 (MIPI_DSI_D3_N), U14.128
MIPI_DSI_REXT: U1.C17 (MIPI_DSI_REXT), U14.122
NAND_ALE: U1.G19 (NAND_ALE), U7.6 (C)
NAND_CE0_B: U1.H19 (NAND_CE0_B), U7.1 (~S)
NAND_CE2_B: U1.F21 (NAND_CE2_B), U15.1 (~S)
NAND_DATA0: U1.G20 (NAND_DATA00), U7.5 (DQ0)
NAND_DATA1: U1.J20 (NAND_DATA01), U7.2 (DQ1)
NAND_DATA2: U1.H22 (NAND_DATA02), U7.3 (~W/DQ2)
NAND_DATA3: U1.J21 (NAND_DATA03), U7.7 (~RESET/DQ3)
NAND_DATA4: U1.L20 (NAND_DATA04), U15.5 (DQ0)
NAND_DATA5: U1.J22 (NAND_DATA05), U15.3 (~W/DQ2)
NAND_DATA6: U1.L19 (NAND_DATA06), U15.2 (DQ1)
NAND_DATA7: U1.M19 (NAND_DATA07), U15.7 (~RESET/DQ3)
NVCC_3V3: C28.2, C29.2, C30.2, C67.2, C68.2, C69.2, C70.2, Q1.2 (S), R12.1, U1.D8 (NVCC_UART), U1.E3 (NVCC_SAI3), U1.F5 (NVCC_ECSPI), U1.F11 (USB2_VPH), U1.F12 (USB1_VPH), U1.G11 (USB2_VDD33), U1.G12 (USB1_VDD33), U1.H7 (NVCC_I2C), U1.H23 (PCIE_VPH), U1.J7 (NVCC_SAI2), U1.J23 (PCIE_VPH), U1.K3 (NVCC_SAI1), U1.L3 (NVCC_SAI1), U1.L18 (NVCC_NAND), U1.M3 (NVCC_SAI5), U1.M18 (NVCC_NAND), U1.R5 (NVCC_GPIO1), U1.R6 (NVCC_GPIO1), U1.W4 (NVCC_JTAG), U1.W18 (NVCC_SNVS), U3.39 (VGEN5), U3.55 (VDDIO), U6.E6 (VCC_E6), U6.F5 (VCC_F5), U6.J10 (VCC_J10), U6.K9 (VCC_K9), U7.8 (VCC), U8.4 (VDD), U8.72 (VDD), U8.73 (VDD), U15.8 (VCC)
NVCC_DRAM_1V1: C18.1, C36.1, C58.1, C74.1, L3.2, U1.AA10 (NVCC_DRAM), U1.AA15 (NVCC_DRAM), U1.AB3 (NVCC_DRAM), U1.AB8 (NVCC_DRAM), U1.AB17 (NVCC_DRAM), U1.AB23 (NVCC_DRAM), U1.AC3 (NVCC_DRAM), U1.AC6 (NVCC_DRAM), U1.AC8 (NVCC_DRAM), U1.AC14 (NVCC_DRAM), U1.AC17 (NVCC_DRAM), U1.AC20 (NVCC_DRAM), U1.AC23 (NVCC_DRAM), U1.AD5 (NVCC_DRAM), U1.AD18 (NVCC_DRAM), U1.AD21 (NVCC_DRAM), U1.Y12 (NVCC_DRAM), U1.Y14 (NVCC_DRAM), U2.A4 (VDD2), U2.A9 (VDD2), U2.AB4 (VDD2), U2.AB9 (VDD2), U2.F5 (VDD2), U2.F8 (VDD2), U2.H1 (VDD2), U2.H5 (VDD2), U2.H8 (VDD2), U2.H12 (VDD2), U2.K1 (VDD2), U2.K3 (VDD2), U2.K10 (VDD2), U2.K12 (VDD2), U2.N1 (VDD2), U2.N3 (VDD2), U2.N10 (VDD2), U2.N12 (VDD2), U2.R1 (VDD2), U2.R5 (VDD2), U2.R8 (VDD2), U2.R12 (VDD2), U2.U5 (VDD2), U2.U8 (VDD2), U3.25 (SW2FB), U3.30 (VINREFDDR)
NVCC_SD1_1V8: C24.2, C25.2, C26.2, C27.2, C31.1, C37.1, C43.1, L4.2, U1.L23 (NVCC_SD1), U1.M23 (NVCC_SD1), U3.19 (SW4FB), U6.C6 (VCCQ_C6), U6.M4 (VCCQ_M4), U6.N4 (VCCQ_N4), U6.P3 (VCCQ_P3), U6.P5 (VCCQ_P5)
unnamed: C79.1, R15.1, R16.2, R17.2
unnamed: C79.2, R14.1, R15.2
unnamed: L8.1, U16.1 (SW), U16.9 (SW)
unnamed: L9.1, U17.1 (SW), U17.9 (SW)
unnamed: R1.1, U1.AA13 (DRAM_ZN)
unnamed: U1.V22 (RTC), X1.3 (RFout)
unnamed: C20.1, R10.2, U1.U25 (XTALI_25M), Y2.1
unnamed: C22.1, R9.2, U1.V25 (XTALI_27M), Y1.3
unnamed: C19.1, R10.1, U1.U24 (XTALO_25M), Y2.3
unnamed: C21.1, R9.1, U1.V24 (XTALO_27M), Y1.1
unnamed: U1.C11 (USB2_VPTX), U1.C12 (USB1_VPTX), U1.D11 (USB2_VP), U1.D12 (USB1_VP), U1.E11 (USB2_DVDD), U1.E12 (USB1_DVDD)
unnamed: R2.1, U2.A5 (ZQ0)
unnamed: L1.1, U3.8 (SW1ALX), U3.9 (SW1BLX)
unnamed: L2.1, U3.11 (SW1CLX), U3.14 (SW1VSSSNS)
unnamed: L3.1, U3.22 (SW2LX)
unnamed: L5.1, U3.35 (SW3BLX), U3.36 (SW3ALX)
unnamed: L4.1, U3.21 (SW4LX)
unnamed: C73.2, U3.49 (VCORE)
unnamed: C71.2, U3.51 (VCOREDIG)
unnamed: C72.2, U3.52 (VCOREREF)
unnamed: R11.2, U3.47 (VDDOTP)
unnamed: C54.1, U3.42 (LICELL)
unnamed: C58.2, C59.1, U3.29 (VHALF)
unnamed: C57.1, U3.40 (VIN3)
unnamed: R5.1, U4.12 (EN)
unnamed: R6.2, R7.1, U4.11 (FB)
unnamed: R3.2, R4.1, U4.6 (MODE)
unnamed: L6.1, U4.7 (SW)
unnamed: C11.1, R3.1, U4.9 (VCC)
unnamed: C78.1, U5.7 (BIAS)
unnamed: C77.1, U5.10 (BST)
unnamed: R12.2, U5.4 (EN)
unnamed: R16.1, U5.14 (FB)
unnamed: R13.2, U5.15 (FREQ)
unnamed: R8.2, U5.6 (PG)
unnamed: C80.1, U5.13 (SS)
unnamed: C77.2, L7.1, U5.9 (SW)
unnamed: C44.1, R8.1, U5.11 (VCC)
unnamed: U9.12 (TX_CON_2+), U10.C1 (CH1_OUT+)
unnamed: U9.11 (TX_CON_2-), U10.C2 (CH1_OUT-)
unnamed: U9.7 (TX_CON_1-), U10.C3 (CH2_OUT+)
unnamed: U9.6 (TX_CON_1+), U10.C4 (CH2_OUT-)
unnamed: U9.2 (RX_CON_1+), U11.C1 (CH1_OUT+)
unnamed: U9.3 (RX_CON_1-), U11.C2 (CH1_OUT-)
unnamed: U9.9 (RX_CON_2+), U11.C3 (CH2_OUT+)
unnamed: U9.8 (RX_CON_2-), U11.C4 (CH2_OUT-)
unnamed: U1.A8 (USB2_RX_P), U11.C5 (CH3_OUT+)
unnamed: U1.A9 (USB2_TX_P), U11.C6 (CH3_OUT-)
unnamed: U1.A10 (USB2_DP), U12.C1 (CH1_OUT+)
unnamed: U1.B10 (USB2_DN), U12.C2 (CH1_OUT-)
unnamed: U1.B8 (USB2_RX_N), U12.C3 (CH2_OUT+)
unnamed: U1.B9 (USB2_TX_N), U12.C4 (CH2_OUT-)
unnamed: R19.2, R20.1, U16.7 (PG)
unnamed: C84.2, U16.4 (RAMP)
unnamed: R18.2, R21.1, U17.7 (PG)
unnamed: C91.2, U17.4 (RAMP)
unnamed: C23.2, X1.1 (Vctrl), X1.4 (VDD)
PCIE1_REF_PAD_CLK_+: U1.K25 (PCIE1_REF_PAD_C_LK_P), U14.296
PCIE1_REF_PAD_CLK_-: U1.K24 (PCIE1_REF_PAD_C_LK_N), U14.294
PCIE1_RESREF: U1.G25 (PCIE1_RESREF), U14.284
PCIE1_RXN_+: U1.H25 (PCIE1_RXN_P), U14.288
PCIE1_RXN_-: U1.H24 (PCIE1_RXN_N), U14.286
PCIE1_TXN_+: U1.J25 (PCIE1_TXN_P), U14.292
PCIE1_TXN_-: U1.J24 (PCIE1_TXN_N), U14.290
PCIE2_REF_PAD_CLK_+: U1.F25 (PCIE2_REF_PAD_C_LK_P), U14.272
PCIE2_REF_PAD_CLK_-: U1.F24 (PCIE2_REF_PAD_C_LK_N), U14.270
PCIE2_RESREF: U1.C25 (PCIE2_RESREF), U14.260
PCIE2_RXN_+: U1.D25 (PCIE2_RXN_P), U14.264
PCIE2_RXN_-: U1.D24 (PCIE2_RXN_N), U14.262
PCIE2_TXN_+: U1.E25 (PCIE2_TXN_P), U14.268
PCIE2_TXN_-: U1.E24 (PCIE2_TXN_N), U14.266
SAI1_RXD0: U1.K2 (SAI1_RXD0), U14.15
SAI1_RXD1: U1.L2 (SAI1_RXD1), U14.13
SAI1_RXD2: U1.H2 (SAI1_RXD2), U14.21
SAI1_RXD3: U1.J2 (SAI1_RXD3), U14.17
SAI1_RXD4: U1.J1 (SAI1_RXD4), U14.19
SAI1_RXD5: U1.F1 (SAI1_RXD5), U14.29
SAI1_RXD6: U1.G2 (SAI1_RXD6), U14.23
SAI1_RXD7: U1.G1 (SAI1_RXD7), U14.25
SAI1_TXD0: U1.F2 (SAI1_TXD0), U14.27
SAI1_TXD1: U1.E2 (SAI1_TXD1), U14.31
SAI1_TXD2: U1.B2 (SAI1_TXD2), U14.43
SAI1_TXD3: U1.D1 (SAI1_TXD3), U14.35
SAI1_TXD4: U1.D2 (SAI1_TXD4), U14.33
SAI1_TXD5: U1.C2 (SAI1_TXD5), U14.37
SAI1_TXD6: U1.B3 (SAI1_TXD6), U14.41
SAI1_TXD7: U1.C1 (SAI1_TXD7), U14.39
SD1_CLK: U1.L25 (SD1_CLK), U6.M6 (CLK)
SD1_CMD: U1.L24 (SD1_CMD), U6.M5 (CMD)
SD1_DATA0: U1.M25 (SD1_DATA0), U6.A3 (DAT0)
SD1_DATA1: U1.M24 (SD1_DATA1), U6.A4 (DAT1)
SD1_DATA2: U1.N25 (SD1_DATA2), U6.A5 (DAT2)
SD1_DATA3: U1.P25 (SD1_DATA3), U6.B2 (DAT3)
SD1_DATA4: U1.N24 (SD1_DATA4), U6.B3 (DAT4)
SD1_DATA5: U1.P24 (SD1_DATA5), U6.B4 (DAT5)
SD1_DATA6: U1.R25 (SD1_DATA6), U6.B5 (DAT6)
SD1_DATA7: U1.T25 (SD1_DATA7), U6.B6 (DAT7)
SD1_STROBE: U1.T24 (SD1_STROBE), U6.H5 (RCLK)
SD1_nRST: U1.R24 (SD1_RESET_B), U6.K5 (RST_N)
UART2_CTS_B: U1.C6 (UART4_RXD), U14.66
UART2_RTS_B: U1.D7 (UART4_TXD), U14.68
UART2_RXD: U1.B6 (UART2_RXD), U14.62
UART2_TXD: U1.D6 (UART2_TXD), U14.64
USB1_DN: U1.B14 (USB1_DN), U10.C6 (CH3_OUT-)
USB1_DP: U1.A14 (USB1_DP), U10.C5 (CH3_OUT+)
USB1_RX_N: U1.B12 (USB1_RX_N), U9.17 (RX_AP_)
USB1_RX_P: U1.A12 (USB1_RX_P), U9.18 (RX_AP_+)
USB1_TX_N: U1.B13 (USB1_TX_N), U9.14 (TX_AP_)
USB1_TX_P: U1.A13 (USB1_TX_P), U9.15 (TX_AP_)
USB2_VBUS: U1.B11 (USB2_RESREF), U1.D9 (USB2_VBUS)
VCAM_1V5: C60.1, U3.16 (VGEN1)
VCAM_2V8: C64.1, U3.41 (VGEN6)
VDDA_1V8: C63.1, U3.28 (VGEN4)
VDD_1v8: U2.AA3 (VDDQ), U2.AA5 (VDDQ), U2.AA8 (VDDQ), U2.AA10 (VDDQ), U2.B3 (VDDQ), U2.B5 (VDDQ), U2.B8 (VDDQ), U2.B10 (VDDQ), U2.D1 (VDDQ), U2.D5 (VDDQ), U2.D8 (VDDQ), U2.D12 (VDDQ), U2.F1 (VDD1), U2.F3 (VDDQ), U2.F10 (VDDQ), U2.F12 (VDD1), U2.G4 (VDD1), U2.G9 (VDD1), U2.T4 (VDD1), U2.T9 (VDD1), U2.U1 (VDD1), U2.U3 (VDDQ), U2.U10 (VDDQ), U2.U12 (VDD1), U2.W1 (VDDQ), U2.W5 (VDDQ), U2.W8 (VDDQ), U2.W12 (VDDQ)
VDD_ARM_0V9: C84.1, C85.1, C86.1, C87.1, L8.2, R20.2, U1.G14 (VDD_ARM), U1.G15 (VDD_ARM), U1.G16 (VDD_ARM), U1.H14 (VDD_ARM), U1.H15 (VDD_ARM), U1.H16 (VDD_ARM), U1.J15 (VDD_ARM), U1.J16 (VDD_ARM), U16.2 (OUT)
VDD_DRAM_0V9: C33.1, C39.1, C45.1, C47.1, L5.2, U1.V9 (VDD_DRAM), U1.Y6 (VDD_DRAM), U1.Y8 (VDD_DRAM), U3.38 (SW3AFB)
VDD_GPU_0V9: C16.1, C34.1, C40.1, C46.1, L1.2, U1.J9 (VDD_GPU), U1.J10 (VDD_GPU), U1.K9 (VDD_GPU), U1.L9 (VDD_GPU), U1.M9 (VDD_GPU), U3.6 (SW1FB)
VDD_PHY_0V9: C61.1, U1.F22 (PCIE_VP), U1.F23 (PCIE_VPTXC), U1.G22 (PCIE_VP), U1.G23 (PCIE_VPTXC), U1.U3 (HDMI_AVDDCORE), U1.U4 (HDMI_AVDDCORE), U1.V3 (HDMI_AVDDCLK), U3.18 (VGEN2)
VDD_PHY_1V8: C62.1, U1.C18 (MIPI_VDDHA), U1.D17 (MIPI_VDDHA), U1.D18 (MIPI_VDDHA), U1.E15 (MIPI_VDD), U1.E17 (MIPI_VDDA), U1.E18 (MIPI_VDDA), U1.F15 (MIPI_VDD), U1.F17 (MIPI_VDDA), U1.F18 (MIPI_VDDA), U1.F19 (MIPI_VDDPLL), U1.P2 (HDMI_AVDDIO), U3.26 (VGEN3)
VDD_SNVS_0V9: C65.1, U3.43 (VSNVS)
VDD_SOC_0V9: C91.1, C92.1, C93.1, C94.1, L9.2, R21.2, U17.2 (OUT)
VDD_SOC_0v9: U1.R8 (VDD_SOC), U1.R9 (VDD_SOC), U1.T8 (VDD_SOC)
VDD_VPU_0V9: C17.1, C35.1, C41.1, L2.2, U1.N8 (VDD_VPU), U1.N9 (VDD_VPU), U1.P9 (VDD_VPU), U3.13 (SW1CBF)
VREFDDR: C66.1, U3.31 (VREFDDR)
VSYS: C12.1, C13.1, C14.1, C15.1, C32.1, C38.1, R5.2, U4.1 (VIN), U5.2 (VIN), U14.4, U14.6, U14.8, U14.10
WIFI/BLE_CTS: U1.D4 (ECSPI1_SS0), U8.54 (UART_CTS)
WIFI/BLE_PCMRF1: U1.J4 (SAI2_RXFS), U8.58 (PCMRF1)
WIFI/BLE_RTS: U1.B4 (ECSPI1_MISO), U8.57 (UART_RTS)
WIFI/BLE_RX: U1.B7 (UART3_TXD), U8.56 (UART_RX)
WIFI/BLE_SDIO_CLK: U1.L22 (SD2_CLK), U8.52 (SDIO_CLK)
WIFI/BLE_SDIO_CMD: U1.M22 (SD2_CMD), U8.51 (SDIO_CMD)
WIFI/BLE_SDIO_DATA0: U1.N22 (SD2_DATA0), U8.50 (SDIO_DATA0)
WIFI/BLE_SDIO_DATA1: U1.N21 (SD2_DATA1), U8.49 (SDIO_DATA1)
WIFI/BLE_SDIO_DATA2: U1.P22 (SD2_DATA2), U8.48 (SDIO_DATA2)
WIFI/BLE_SDIO_DATA3: U1.P21 (SD2_DATA3), U8.47 (SDIO_DATA3)
WIFI/BLE_SDIO_PCMCLK: U1.J5 (SAI2_TXC), U8.61 (PCMCLK)
WIFI/BLE_SDIO_PCMIN: U1.G5 (SAI2_TXD0), U8.59 (PCMIN)
WIFI/BLE_SDIO_PCMOUT: U1.H6 (SAI2_RXD0), U8.60 (PCMOUT)
WIFI/BLE_SDIO_STROBE: U1.M21 (SD2_WP), U8.46 (SDIO_WAKE#)
WIFI/BLE_SDIO_nRST: U1.R22 (SD2_RESET_B), U8.45 (SDIO_RESET#)
WIFI/BLE_TX: U1.A6 (UART3_RXD), U8.55 (UART_TX)
